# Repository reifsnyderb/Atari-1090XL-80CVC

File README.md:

# 80cvc
80 column card for Atari 1090XL expansion box

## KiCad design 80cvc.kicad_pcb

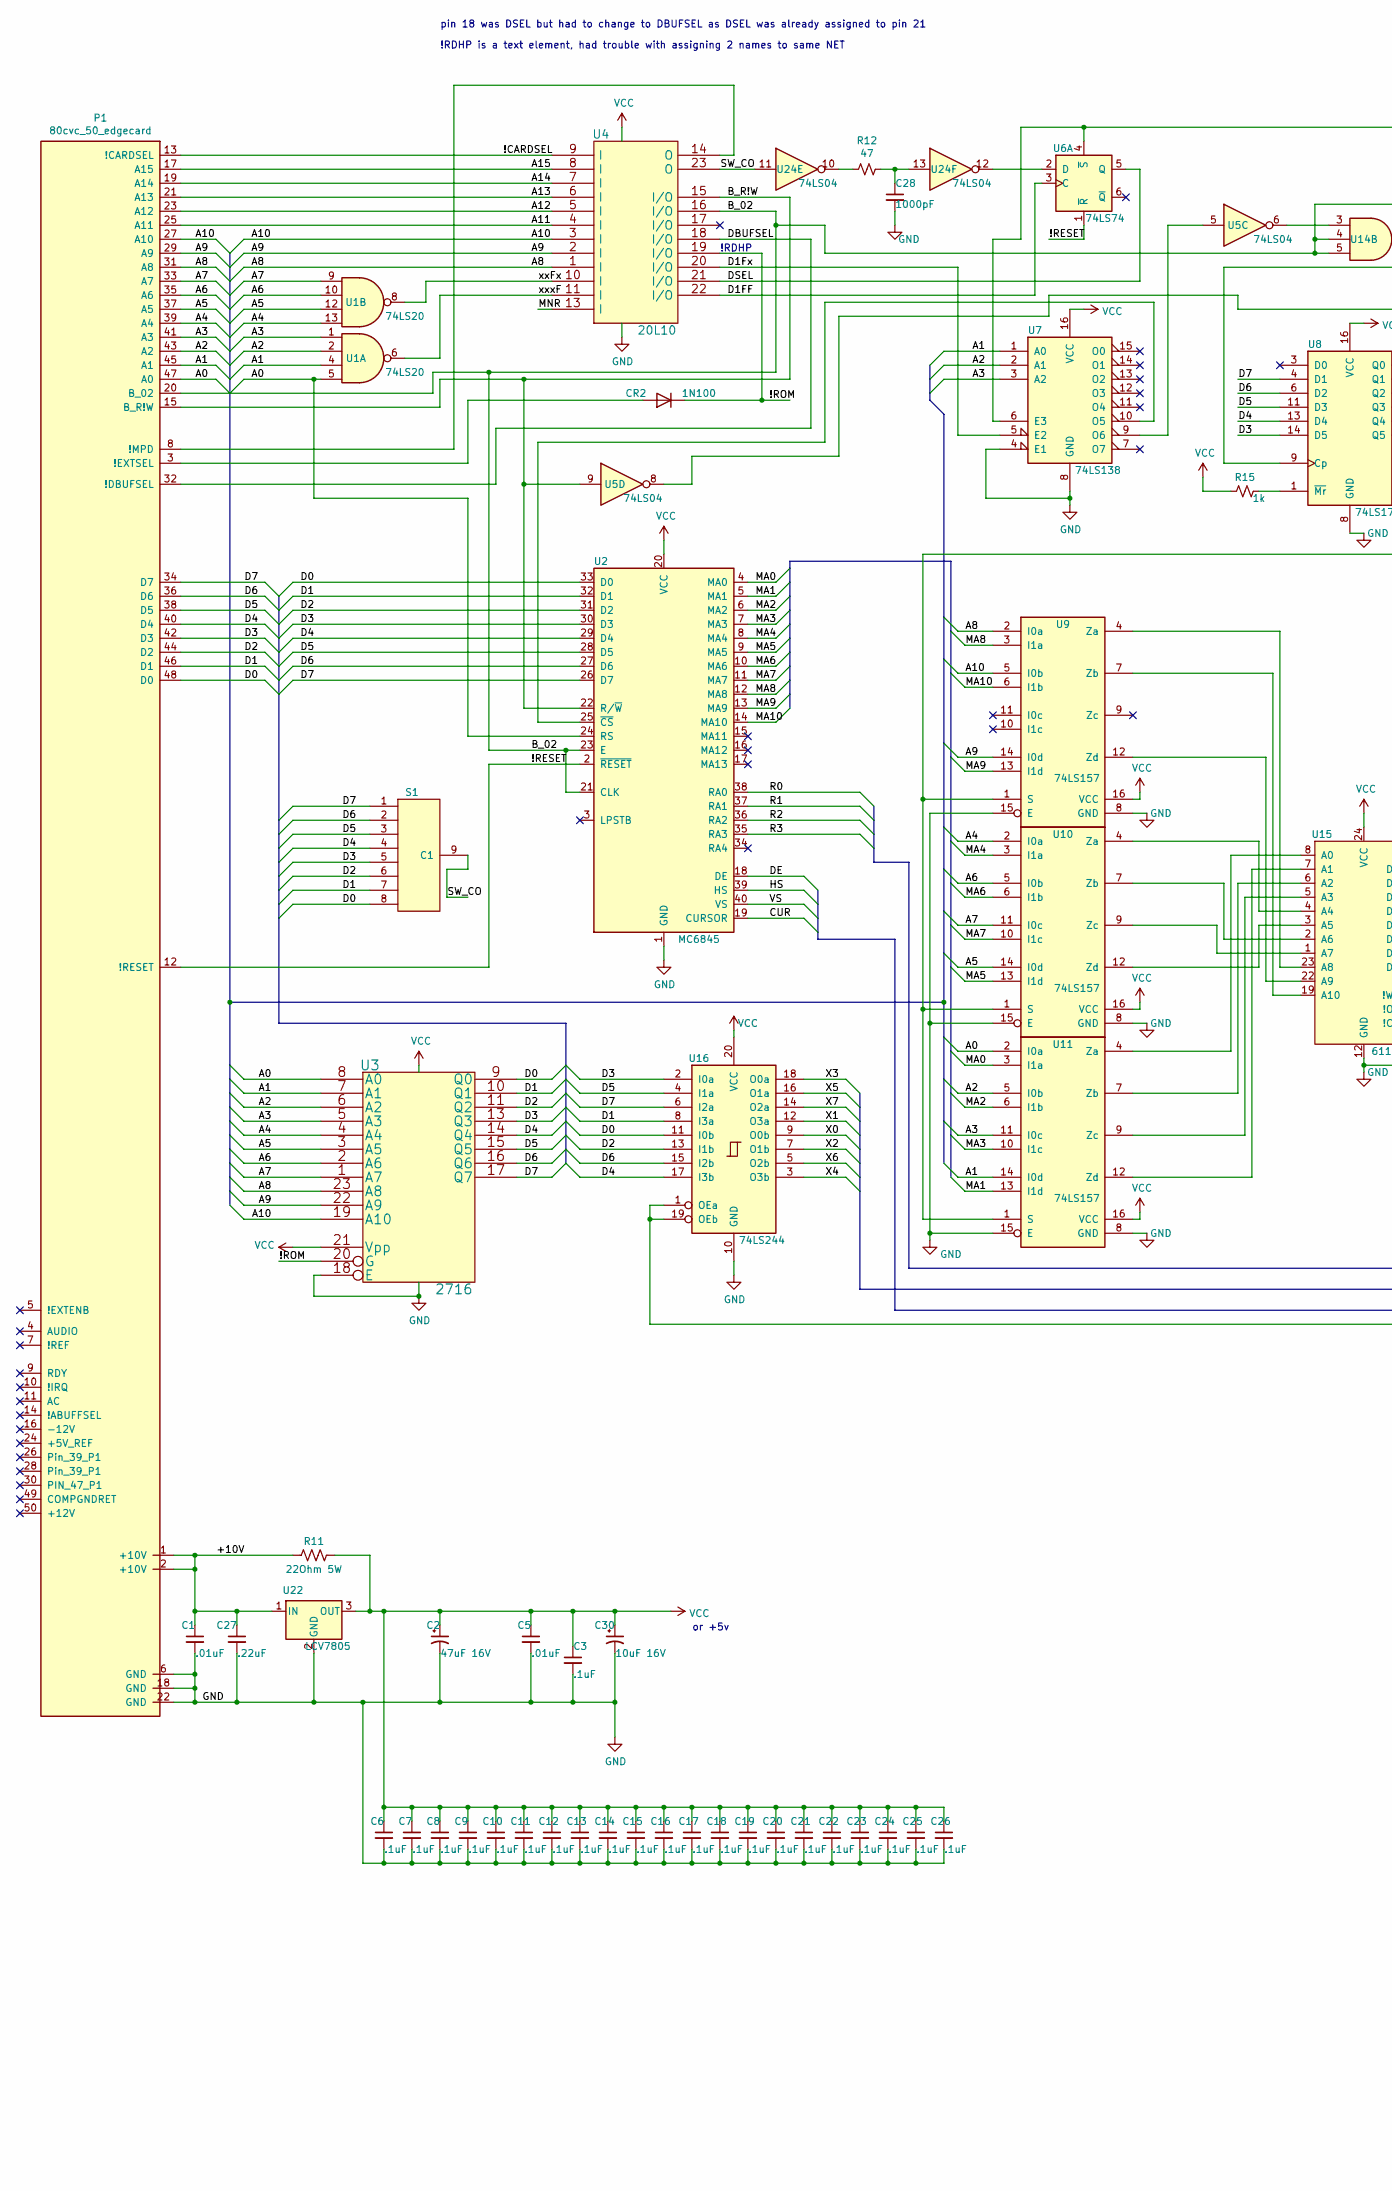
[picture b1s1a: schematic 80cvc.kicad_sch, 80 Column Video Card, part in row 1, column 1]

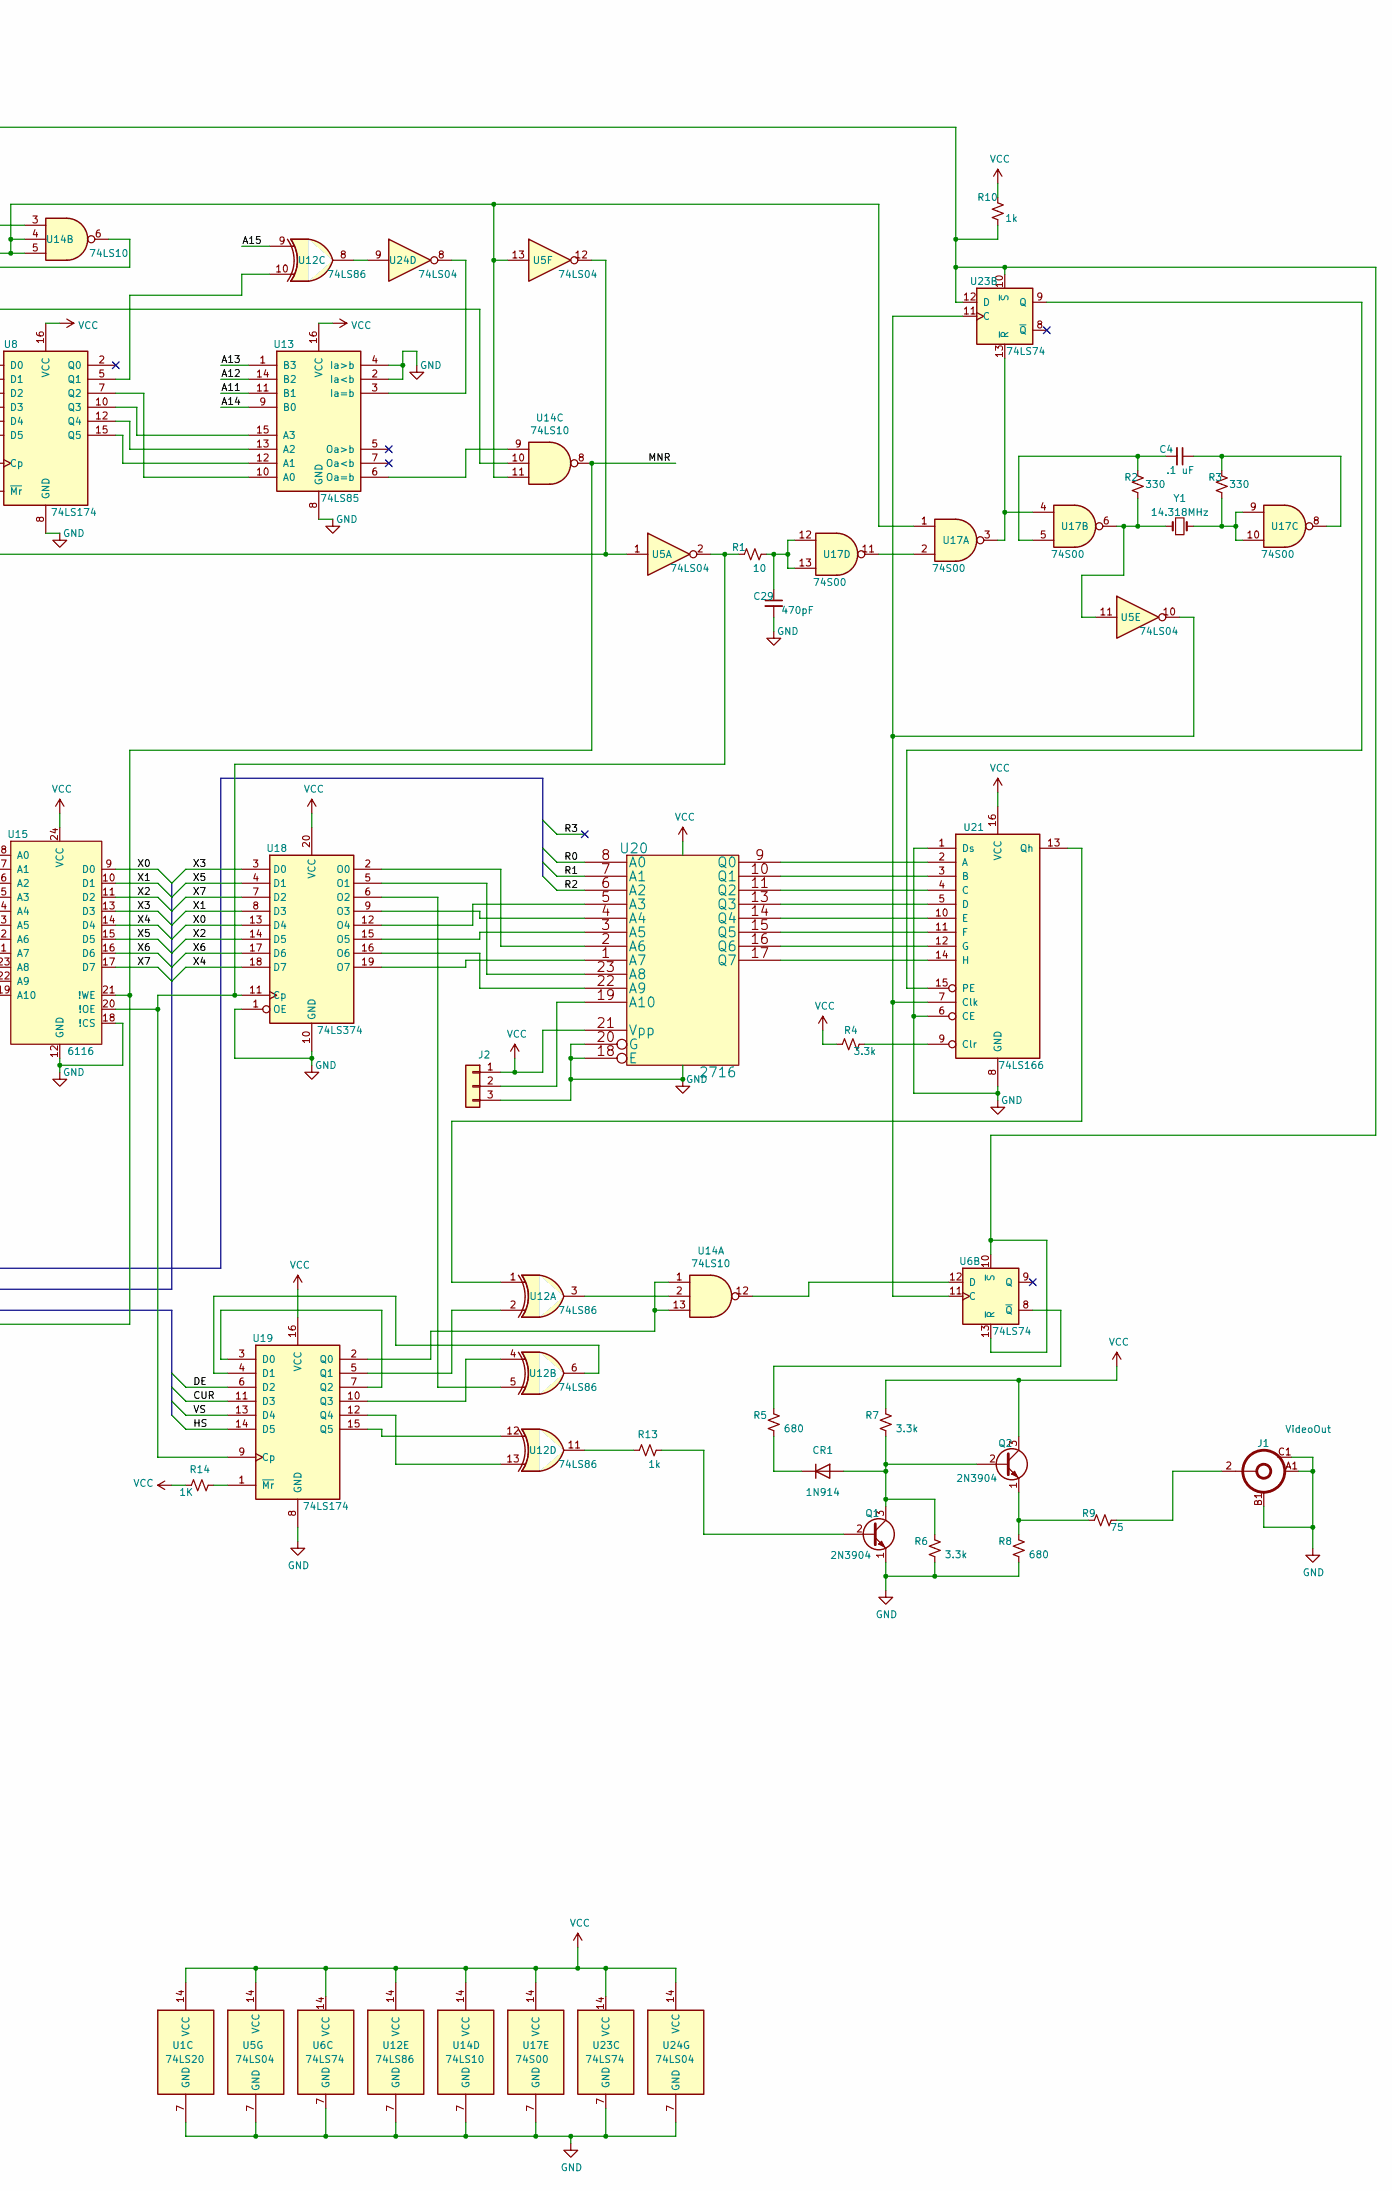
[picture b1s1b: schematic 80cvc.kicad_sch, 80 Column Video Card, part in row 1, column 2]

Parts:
C1, C5: .01uF; C_Axial_L3.8mm_D2.6mm_P7.50mm_Horizontal; Mfr Part # A103K15X7RF5TAA; Mouser Part # 594-A103K15X7RF5TAA
C2: 47uF 16V; CP_Axial_L10.0mm_D4.5mm_P15.00mm_Horizontal; Mfr Part # MAL203036479E3; Mouser Part # 594-2222-030-36479
C3, C6, C7, C8, C9, C10, C11, C12, C13, C14, C15, C16, C17, C18, C19, C20, C21, C22, C23, C24, C25, C26: .1uF; C_Axial_L3.8mm_D2.6mm_P7.50mm_Horizontal; Mfr Part # A104K15X7RF5TAA; Mouser Part # 594-A104K15X7RF5TAA
C4: .1 uF; C_Axial_L3.8mm_D2.6mm_P7.50mm_Horizontal; Mfr Part # A104K15X7RF5TAA; Mouser Part # 594-A104K15X7RF5TAA
C27: .22uF; C_Axial_L3.8mm_D2.6mm_P7.50mm_Horizontal; Mfr Part # A224K20X7RF5TAA; Mouser Part # 594-A224K20X7RF5TAA
C28: 1000pF; C_Rect_L7.0mm_W2.0mm_P5.00mm; Mfr Part # A102K15X7RF5TAA; Mouser Part # 594-A102K15X7RF5TAA
C29: 470pF; C_Rect_L7.0mm_W2.0mm_P5.00mm; Mfr Part # A471K15X7RF5UAA; Mouser Part # 594-A471K15X7RF5UAA
C30: 10uF 16V; CP_Radial_D5.0mm_P2.50mm; Mfr Part # ECA-1EEN100; Mouser Part # 667-ECA-1EEN100
CR1: 1N914; D_DO-35_SOD27_P10.16mm_Horizontal
CR2: 1N100; D_DO-35_SOD27_P10.16mm_Horizontal
J1: VideoOut; RCJ014; Mfr Part # RCJ014; Mouser Part # 490-RCJ-014
J2: Conn_01x03; PinHeader_1x03_P2.54mm_Vertical; Mfr Part # 826629-3; Mouser Part # 571-826629-3
P1: 80cvc_50_edgecard; Edge-50; Mfr Part # Part of PCB
Q1, Q2: 2N3904; TO-92_Inline; Mfr Part # 2N3904BU; Mouser Part # 512-2N3904BU
R1: 10; R_Axial_DIN0207_L6.3mm_D2.5mm_P10.16mm_Horizontal; Mfr Part # CF1/4CT52R100J; Mouser Part # 660-CF1/4CT52R100J
R2, R3: 330; R_Axial_DIN0207_L6.3mm_D2.5mm_P10.16mm_Horizontal; Mfr Part # 291-330/AP-RC; Mouser Part # 291-330/AP-RC
R4, R6, R7: 3.3k; R_Axial_DIN0207_L6.3mm_D2.5mm_P10.16mm_Horizontal; Mfr Part # CFR-25JB-52-3K3; Mouser Part # 603-CFR-25JB-52-3K3
R5, R8: 680; R_Axial_DIN0207_L6.3mm_D2.5mm_P10.16mm_Horizontal; Mfr Part # CFR-25JB-52-680R; Mouser Part # 603-CFR-25JB-52-680R
R9: 75; R_Axial_DIN0207_L6.3mm_D2.5mm_P10.16mm_Horizontal; Mfr Part # CFR-25JB-52-75R; Mouser Part # 603-CFR-25JB-52-75R
R10, R13, R15: 1k; R_Axial_DIN0207_L6.3mm_D2.5mm_P10.16mm_Horizontal; Mfr Part # 291-1K-RC; Mouser Part # 291-1K-RC
R11: 22Ohm 5W; R_Axial_DIN0414_L11.9mm_D4.5mm_P20.32mm_Horizontal; Mfr Part # AC05000002209JAC00; Mouser Part # 594-AC05W22R00J
R12: 47; R_Axial_DIN0207_L6.3mm_D2.5mm_P10.16mm_Horizontal; Mfr Part # CF1/4CT52R470; Mouser Part # 660-CF1/4CT52R470J
R14: 1K; R_Axial_DIN0207_L6.3mm_D2.5mm_P10.16mm_Horizontal; Mfr Part # 291-1K-RC; Mouser Part # 291-1K-RC
S1: Sw-Rotary-1P8T; RS18; Mfr Part # RS-18; Mouser Part # 107-RS-18
U1: 74LS20; DIP-14_W7.62mm
U2: MC6845; DIP-40_W15.24mm; Mfr Part # MC68B45
U3, U20: 2716; DIP-24_W15.24mm; Mfr Part # 2716
U4: 20L10; DIP-24_W7.62mm; Mfr Part # 22v10
U5, U24: 74LS04; DIP-14_W7.62mm
U6: 74LS74; DIP-14_W7.62mm; Mfr Part # SN74LS74AN; Mouser Part # 595-SN74LS74AN
U7: 74LS138; DIP-16_W7.62mm; Mfr Part # SN74LS138N; Mouser Part # 595-SN74LS138N
U8, U19: 74LS174; DIP-16_W7.62mm; Mfr Part # SN74LS174N; Mouser Part # 595-SN74LS174N
U9, U10, U11: 74LS157; DIP-16_W7.62mm; Mfr Part # SN74LS157N; Mouser Part # 595-SN74LS157N
U12: 74LS86; DIP-14_W7.62mm; Mfr Part # SN74LS86AN; Mouser Part # 595-SN74LS86AN
U13: 74LS85; DIP-16_W7.62mm; Mfr Part # SN74LS85N; Mouser Part # 595-SN74LS85N
U14: 74LS10; DIP-14_W7.62mm
U15: 6116; DIP-24_W15.24mm; Mfr Part # 6116
U16: 74LS244; DIP-20_W7.62mm; Mfr Part # SN74LS244N; Mouser Part # 595-SN74LS244N
U17: 74S00; DIP-14_W7.62mm
U18: 74LS374; DIP-20_W7.62mm; Mfr Part # SN74LS374N; Mouser Part # 595-SN74LS374N
U21: 74LS166; DIP-16_W7.62mm; Mfr Part # SN74LS166AN; Mouser Part # 595-SN74LS166AN
U22: LCV7805; TO-220F-3_Horizontal_TabDown; Mfr Part # L7805CV-DG; Mouser Part # 511-L7805CV-DG
U23: 74LS74; DIP-14_W7.62mm
Y1: 14.318MHz; Crystal_HC18-U_Horizontal; Mfr Part # MP143; Mouser Part # 774-MP143

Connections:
/!CARDSEL: P1.13 (!CARDSEL), U4.9 (I)
/!RESET: P1.12 (!RESET), U2.2 (~RESET), U6.1 (~R)
/!ROM: CR2.1 (K), U3.20 (G), U4.19 (I/O)
/+10V: C1.1, C27.1, P1.1 (+10V), P1.2 (+10V), R11.2, U22.1 (IN)
/A0: P1.47 (A0), U1.5, U2.24 (RS), U3.8 (A0), U11.2 (I0a)
/A1: P1.45 (A1), U1.4, U3.7 (A1), U7.1 (A0), U11.14 (I0d)
/A2: P1.43 (A2), U1.2, U3.6 (A2), U7.2 (A1), U11.5 (I0b)
/A3: P1.41 (A3), U1.1, U3.5 (A3), U7.3 (A2), U11.11 (I0c)
/A4: P1.39 (A4), U1.13, U3.4 (A4), U10.2 (I0a)
/A5: P1.37 (A5), U1.12, U3.3 (A5), U10.14 (I0d)
/A6: P1.35 (A6), U1.10, U3.2 (A6), U10.5 (I0b)
/A7: P1.33 (A7), U1.9, U3.1 (A7), U10.11 (I0c)
/A8: P1.31 (A8), U3.23 (A8), U4.1 (I), U9.2 (I0a)
/A9: P1.29 (A9), U3.22 (A9), U4.2 (I), U9.14 (I0d)
/A10: P1.27 (A10), U3.19 (A10), U4.3 (I), U9.5 (I0b)
/A11: P1.25 (A11), U4.4 (I), U13.11 (B1)
/A12: P1.23 (A12), U4.5 (I), U13.14 (B2)
/A13: P1.21 (A13), U4.6 (I), U13.1 (B3)
/A14: P1.19 (A14), U4.7 (I), U13.9 (B0)
/A15: P1.17 (A15), U4.8 (I), U12.9
/B_02: P1.20 (B_02), U2.21 (CLK), U2.23 (E), U4.16 (I/O), U5.13, U14.4, U14.5, U14.11, U17.1
/B_R!W: P1.15 (B_R!W), U2.22 (R/~W), U4.15 (I/O), U5.9
/CUR: U2.19 (CURSOR), U19.11 (D3)
/D0: P1.48 (D0), S1.8, U2.33 (D0), U3.9 (Q0), U16.11 (I0b)
/D1: P1.46 (D1), S1.7, U2.32 (D1), U3.10 (Q1), U16.8 (I3a)
/D1FF: U4.22 (I/O), U6.3 (C)
/D1Fx: U4.20 (I/O), U7.5 (E2)
/D2: P1.44 (D2), S1.6, U2.31 (D2), U3.11 (Q2), U16.13 (I1b)
/D3: P1.42 (D3), S1.5, U2.30 (D3), U3.13 (Q3), U8.14 (D5), U16.2 (I0a)
/D4: P1.40 (D4), S1.4, U2.29 (D4), U3.14 (Q4), U8.13 (D4), U16.17 (I3b)
/D5: P1.38 (D5), S1.3, U2.28 (D5), U3.15 (Q5), U8.11 (D3), U16.4 (I1a)
/D6: P1.36 (D6), S1.2, U2.27 (D6), U3.16 (Q6), U8.6 (D2), U16.15 (I2b)
/D7: P1.34 (D7), S1.1, U2.26 (D7), U3.17 (Q7), U8.4 (D1), U16.6 (I2a)
/DBUFSEL: P1.32 (!DBUFSEL), U4.18 (I/O)
/DE: U2.18 (DE), U19.6 (D2)
/DSEL: U4.21 (I/O), U6.5 (Q)
/HS: U2.39 (HS), U19.14 (D5)
/MA0: U2.4 (MA0), U11.3 (I1a)
/MA1: U2.5 (MA1), U11.13 (I1d)
/MA2: U2.6 (MA2), U11.6 (I1b)
/MA3: U2.7 (MA3), U11.10 (I1c)
/MA4: U2.8 (MA4), U10.3 (I1a)
/MA5: U2.9 (MA5), U10.13 (I1d)
/MA6: U2.10 (MA6), U10.6 (I1b)
/MA7: U2.11 (MA7), U10.10 (I1c)
/MA8: U2.12 (MA8), U9.3 (I1a)
/MA9: U2.13 (MA9), U9.13 (I1d)
/MA10: U2.14 (MA10), U9.6 (I1b)
/MNR: U4.13 (I), U14.8, U15.21 (!WE), U16.1 (OEa), U16.19 (OEb)
/R0: U2.38 (RA0), U20.8 (A0)
/R1: U2.37 (RA1), U20.7 (A1)
/R2: U2.36 (RA2), U20.6 (A2)
/R3: U2.35 (RA3)
/SW_CO: S1.9 (C1), U4.23 (O), U24.11
/VS: U2.40 (VS), U19.13 (D4)
/X0: U15.9 (D0), U16.9 (O0b), U18.13 (D4)
/X1: U15.10 (D1), U16.12 (O3a), U18.8 (D3)
/X2: U15.11 (D2), U16.7 (O1b), U18.14 (D5)
/X3: U15.13 (D3), U16.18 (O0a), U18.3 (D0)
/X4: U15.14 (D4), U16.3 (O3b), U18.18 (D7)
/X5: U15.15 (D5), U16.16 (O1a), U18.4 (D1)
/X6: U15.16 (D6), U16.5 (O2b), U18.17 (D6)
/X7: U15.17 (D7), U16.14 (O2a), U18.7 (D2)
/xxFx: U1.8, U4.10 (I)
/xxxF: U1.6, U4.11 (I)
GND: C1.2, C2.2, C3.2, C5.2, C6.2, C7.2, C8.2, C9.2, C10.2, C11.2, C12.2, C13.2, C14.2, C15.2, C16.2, C17.2, C18.2, C19.2, C20.2, C21.2, C22.2, C23.2, C24.2, C25.2, C26.2, C27.2, C28.2, C29.2, C30.2, J1.A1, J1.B1, J1.C1, J2.3, P1.6 (GND), P1.18 (GND), P1.22 (GND), Q1.1 (E), R6.2, R8.2, U1.7 (GND), U2.1 (GND), U3.12 (GND), U3.18 (E), U4.12 (GND), U5.7 (GND), U6.7 (GND), U7.4 (E1), U7.8 (GND), U8.8 (GND), U9.8 (GND), U9.15 (E), U10.8 (GND), U10.15 (E), U11.8 (GND), U11.15 (E), U12.7 (GND), U13.2 (Ia<b), U13.4 (Ia>b), U13.8 (GND), U14.7 (GND), U15.12 (GND), U15.18 (!CS), U16.10 (GND), U17.7 (GND), U18.1 (OE), U18.10 (GND), U19.8 (GND), U20.12 (GND), U20.18 (E), U20.20 (G), U21.1 (Ds), U21.6 (CE), U21.8 (GND), U22.2 (GND), U23.7 (GND), U24.7 (GND)
unnamed: C4.1, R3.1, U17.8
unnamed: C4.2, R2.1, U17.5
unnamed: C28.1, R12.1, U24.13
unnamed: C29.1, R1.2, U17.12, U17.13
unnamed: CR1.2 (A), Q1.3 (C), Q2.2 (B), R6.1, R7.2
unnamed: CR1.1 (K), R5.2
unnamed: CR2.2 (A), P1.3 (!EXTSEL)
unnamed: J1.2, R9.1
unnamed: J2.2, U20.19 (A10)
unnamed: P1.8 (!MPD), U4.14 (O)
unnamed: Q1.2 (B), R13.1
unnamed: Q2.1 (E), R8.1, R9.2
unnamed: R2.2, U5.11, U17.6, Y1.1
unnamed: R3.2, U17.9, U17.10, Y1.2
unnamed: R12.2, U24.10
unnamed: R13.2, U12.11
unnamed: U2.25 (~CS), U7.10 (O5)
unnamed: U6.2 (D), U24.12
unnamed: U6.12 (D), U14.12
unnamed: R5.1, U6.8 (~Q)
unnamed: U5.5, U7.9 (O6)
unnamed: U8.9 (Cp), U14.6
unnamed: U8.5 (Q1), U12.10
unnamed: R15.1, U8.1 (~Mr)
unnamed: U5.1, U5.12, U9.1 (S), U10.1 (S), U11.1 (S)
unnamed: U10.4 (Za), U15.4 (A4)
unnamed: U10.7 (Zb), U15.2 (A6)
unnamed: U10.9 (Zc), U15.1 (A7)
unnamed: U10.12 (Zd), U15.3 (A5)
unnamed: U11.4 (Za), U15.8 (A0)
unnamed: U11.7 (Zb), U15.6 (A2)
unnamed: U11.9 (Zc), U15.5 (A3)
unnamed: U11.12 (Zd), U15.7 (A1)
unnamed: U12.3, U14.2
unnamed: U12.8, U24.9
unnamed: U8.7 (Q2), U13.10 (A0)
unnamed: U8.15 (Q5), U13.12 (A1)
unnamed: U8.12 (Q4), U13.13 (A2)
unnamed: U8.10 (Q3), U13.15 (A3)
unnamed: U13.3 (Ia=b), U24.8
unnamed: U13.6 (Oa=b), U14.9
unnamed: U5.6, U14.3
unnamed: U5.8, U14.10
unnamed: R1.1, U5.2, U15.20 (!OE), U18.11 (Cp), U19.9 (Cp)
unnamed: U9.4 (Za), U15.23 (A8)
unnamed: U9.12 (Zd), U15.22 (A9)
unnamed: U9.7 (Zb), U15.19 (A10)
unnamed: U17.2, U17.11
unnamed: U18.2 (O0), U20.2 (A6)
unnamed: U18.5 (O1), U20.23 (A8)
unnamed: U12.5, U18.6 (O2)
unnamed: U18.9 (O3), U20.4 (A4)
unnamed: U18.12 (O4), U20.5 (A3)
unnamed: U18.15 (O5), U20.3 (A5)
unnamed: U18.16 (O6), U20.22 (A9)
unnamed: U18.19 (O7), U20.1 (A7)
unnamed: U19.3 (D0), U19.7 (Q2)
unnamed: U12.6, U19.4 (D1)
unnamed: U14.1, U14.13, U19.2 (Q0)
unnamed: U12.2, U19.5 (Q1)
unnamed: U12.4, U19.10 (Q3)
unnamed: U12.13, U19.12 (Q4)
unnamed: U12.12, U19.15 (Q5)
unnamed: R14.1, U19.1 (~Mr)
unnamed: U20.9 (Q0), U21.2 (A)
unnamed: U20.10 (Q1), U21.3 (B)
unnamed: U20.11 (Q2), U21.4 (C)
unnamed: U20.13 (Q3), U21.5 (D)
unnamed: U20.14 (Q4), U21.10 (E)
unnamed: U20.15 (Q5), U21.11 (F)
unnamed: U20.16 (Q6), U21.12 (G)
unnamed: U20.17 (Q7), U21.14 (H)
unnamed: U5.10, U6.11 (C), U21.7 (Clk), U23.11 (C)
unnamed: R4.1, U21.9 (Clr)
unnamed: U21.15 (PE), U23.9 (Q)
unnamed: U12.1, U21.13 (Qh)
unnamed: R10.2, U6.4 (~S), U6.10 (~S), U6.13 (~R), U7.6 (E3), U23.10 (~S), U23.12 (D)
unnamed: U17.3, U17.4, U23.13 (~R)
VCC: C2.1, C3.1, C5.1, C6.1, C7.1, C8.1, C9.1, C10.1, C11.1, C12.1, C13.1, C14.1, C15.1, C16.1, C17.1, C18.1, C19.1, C20.1, C21.1, C22.1, C23.1, C24.1, C25.1, C26.1, C30.1, J2.1, Q2.3 (C), R4.2, R7.1, R10.1, R11.1, R14.2, R15.2, U1.14 (VCC), U2.20 (VCC), U3.21 (Vpp), U3.24 (VCC), U4.24 (VCC), U5.14 (VCC), U6.14 (VCC), U7.16 (VCC), U8.16 (VCC), U9.16 (VCC), U10.16 (VCC), U11.16 (VCC), U12.14 (VCC), U13.16 (VCC), U14.14 (VCC), U15.24 (VCC), U16.20 (VCC), U17.14 (VCC), U18.20 (VCC), U19.16 (VCC), U20.21 (Vpp), U20.24 (VCC), U21.16 (VCC), U22.3 (OUT), U23.14 (VCC), U24.14 (VCC)

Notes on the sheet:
!RDHP
!RDHP is a text element, had trouble with assigning 2 names to same NET
pin 18 was DSEL but had to change to DBUFSEL as DSEL was already assigned to pin 21
or +5v

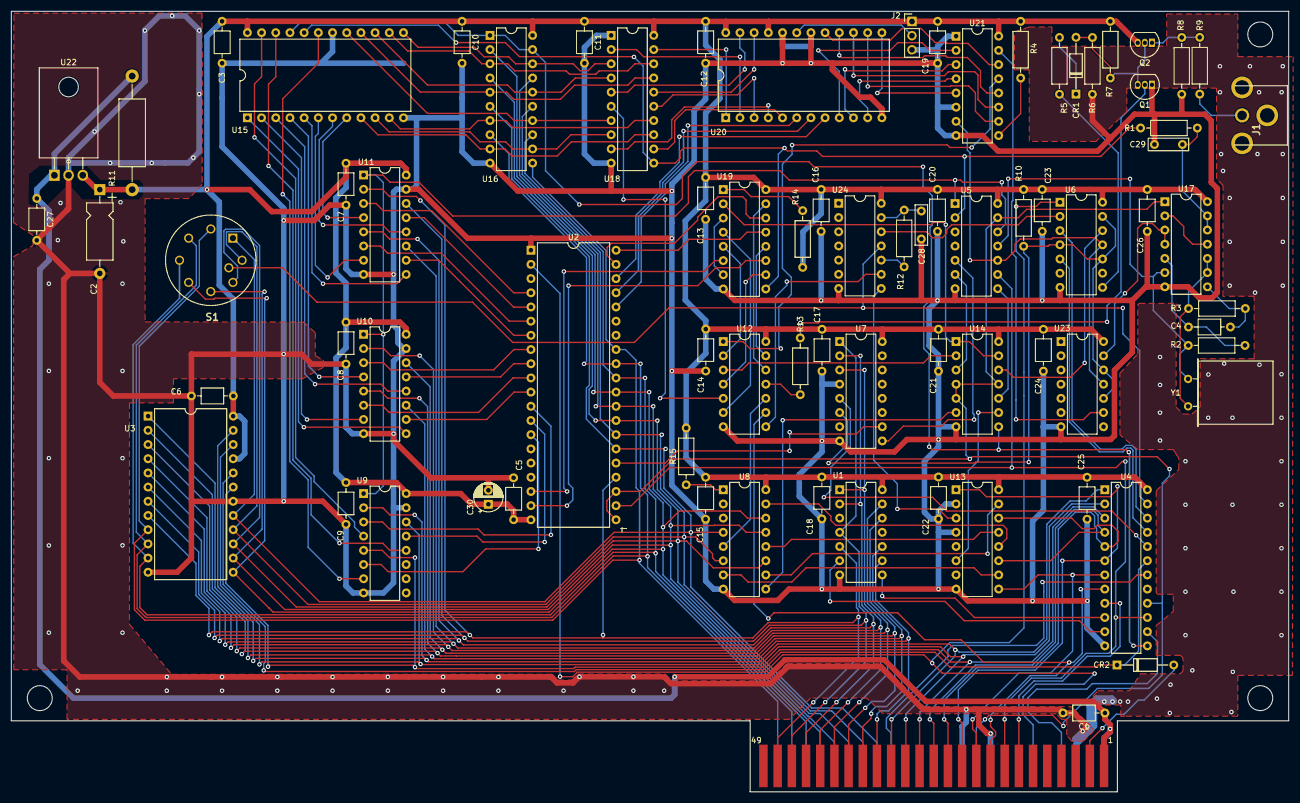
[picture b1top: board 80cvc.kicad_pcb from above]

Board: 2 copper layers, 228.6 x 139.7 mm, 78 parts (0 on the bottom side), 144 nets.
